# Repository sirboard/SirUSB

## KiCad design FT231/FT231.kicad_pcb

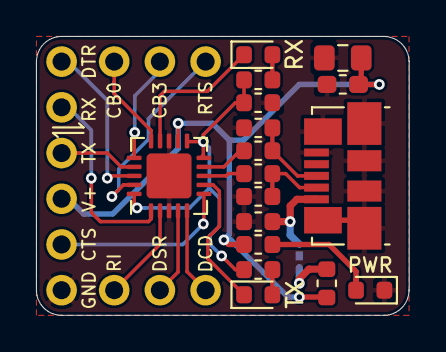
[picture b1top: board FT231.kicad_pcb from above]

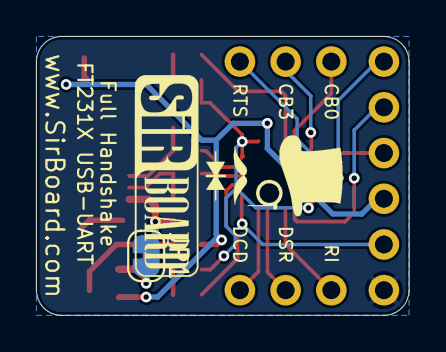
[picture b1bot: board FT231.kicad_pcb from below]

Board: 2 copper layers, 20.7 x 15.5 mm, 21 parts (2 on the bottom side), 24 nets.

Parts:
C1: 10nF; C_0603_1608Metric
C2, C3: 47pF; C_0603_1608Metric
C4: 100nF; C_0603_1608Metric_Pad1.05x0.95mm_HandSolder
C5: 4.7uF; C_0805_2012Metric_Pad1.15x1.40mm_HandSolder
C6: 100nF; C_0603_1608Metric
FB1: 40E@100MHz; L_0603_1608Metric
J1: USB_B_Micro; USB_Micro-B_Molex_47346-0001
J2, J3: Conn_01x03; PinHeader_1x03_P2.54mm_Vertical
J4: Conn_01x06; PinHeader_1x06_P2.54mm_Vertical
JP1: SolderJumper_2_Bridged; SolderJumper-2_P1.3mm_Bridged_RoundedPad1.0x1.5mm
PWR: RED; LED_0603_1608Metric
R1, R2: 27e; R_0603_1608Metric
R3, R4, R5: 680E; R_0603_1608Metric
RX: GREEN; LED_0603_1608Metric
TX: GREEN; LED_0603_1608Metric
U1: FT231XQ; QFN-20-1EP_4x4mm_P0.5mm_EP2.5x2.5mm

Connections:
/5V: C4.1, C5.1, FB1.1, J4.3, R4.1, U1.12
/CB0: J3.1, U1.15
/CB3: J3.2, U1.16
/CTS: J4.2, U1.6
/D+: C2.1, J1.3, R1.1
/D-: C3.1, J1.2, R2.2
/DCD: J2.3, U1.5
/DSR: J2.2, U1.4
/DTR: J4.6, U1.18
/RI: J2.1, U1.2
/RTS: J3.3, U1.19
/RX: J4.5, U1.1
/RXLED: RX.1, U1.14
/TX: J4.4, U1.17
/TXLED: TX.1, U1.7
/uD+: R1.2, U1.9
/uD-: R2.1, U1.8
GND: C1.2, C2.2, C3.2, C4.2, C5.2, C6.2, J1.5, J1.6, J4.1, PWR.1, U1.3, U1.13, U1.21
unnamed: C1.1, J1.1, JP1.1
unnamed: C6.1, R3.1, R5.1, U1.10, U1.11, U1.20
unnamed: FB1.2, JP1.2
unnamed: PWR.2, R4.2
unnamed: R3.2, RX.2
unnamed: R5.2, TX.2

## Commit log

2019-07-16 USB to UART Modules
2019-07-16 remove submodule
2019-07-16 fixed git issue
    fuck windows
2019-07-25 Silkscreens Updated
2019-07-26 Silkscreen Updates
2019-08-06 Dimensions Updated
2019-08-20 Power LED Added
2019-09-09 Power LED edited
2019-09-19 Silkscreen Edits
    Dimensions moved to Drawings Layer
2019-12-02 Page Settings Updated
2019-12-04 Part Numbers Added
2020-01-08 Schematic PDF and 3D Renders added
2020-01-17 CH330N Initial Commit
2020-01-17 CH340E Initial Commit
2020-01-17 CH340G Revision 2
2020-02-08 Board Sizes Reduced in Width by 0.254mm
2020-02-08 FTDI Boards With USB-C Initial Commit
2020-03-12 Soldermask width adjusted
2020-03-12 SirUSB Updates
    3D Renders changed to white solder mask. CH330N TX and RX references moved
2020-04-07 CH340G Fix
    5k1 Resistors added to CC1 and CC2, TX and RX LEDs pulled up to VCC,Copper Pour changed from 3V3 to VCC.
2020-04-07 CH340E Fix
    5k1 Resistors added to CC1 and CC2, TX and RX LEDs pulled up to VCC,Copper Pour changed from 3V3 to VCC.
2020-04-11 SiRUSB Updates
    USB-C 3D Renders Added and Pictures Updated
2020-04-12 SirUSB Updates
    CH330N Revision 1.1 + 3D Render Improvement
2020-04-12 CH3XX Boards Schematics Updated
    .pdf update
2020-04-12 CP2104 Initial Commit
    Silicon Labs USB-UART Converter
2020-04-21 CP2102N_QFN20 Initial Commit
2020-04-21 SirUSB Board Revisions
    Removed MicroUSB Versions of FT230 and FT231, SolderPaste Layer Adjusted to -0.05mm, Silkscreens optimised, OSHW logo added.
